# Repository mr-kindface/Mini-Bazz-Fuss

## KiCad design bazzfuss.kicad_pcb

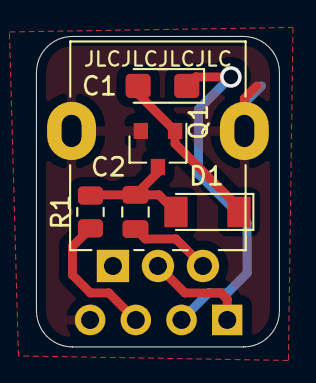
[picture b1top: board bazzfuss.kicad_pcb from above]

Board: 2 copper layers, 13.5 x 17.2 mm, 7 parts (1 on the bottom side), 7 nets.

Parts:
C1: 4.7uf; CP_EIA-3216-10_Kemet-I
C2: 100n; C_0805_2012Metric
D1: LL4148; D_MiniMELF
J1: Conn_01x04; PinHeader_1x04_P2.54mm_Vertical_nooutline
Q1: NPN; SOT-23
R1: 10K; R_0805_2012Metric
RV1: R_POT; Potentiometer_Alpha_RD901F-40-00D_Single_Vertical

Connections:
GND: J1.4, Q1.2, RV1.1
unnamed: C1.1, J1.2
unnamed: C1.2, D1.1, Q1.1
unnamed: C2.1, RV1.3
unnamed: C2.2, D1.2, Q1.3, R1.2
unnamed: J1.1, RV1.2
unnamed: J1.3, R1.1
